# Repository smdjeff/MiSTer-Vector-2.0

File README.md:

## MisterArcade
## DE10-Nano adapter board for vector graphics output

* Modern, 3W mono onboard amplifier
* No slow or overclocked serial DACs. Latched, high speed, low cost R–2R ladder to perform digital-to-analog conversion
* Uses DE10-Nano GPIO1 2x20 connector for input from FPGA (GPIO2 remains free for standard MisterArcade RAM expansion)
* No USB latency
* JAMMA IO with ESD protection

* 10bit +/- 10v X output
* 10bit +/- 10v Y output
* 6bit 0-3.3v RED output
* 6bit 0-3.3v GREEN output
* 6bit 0-3.3v BLUE output

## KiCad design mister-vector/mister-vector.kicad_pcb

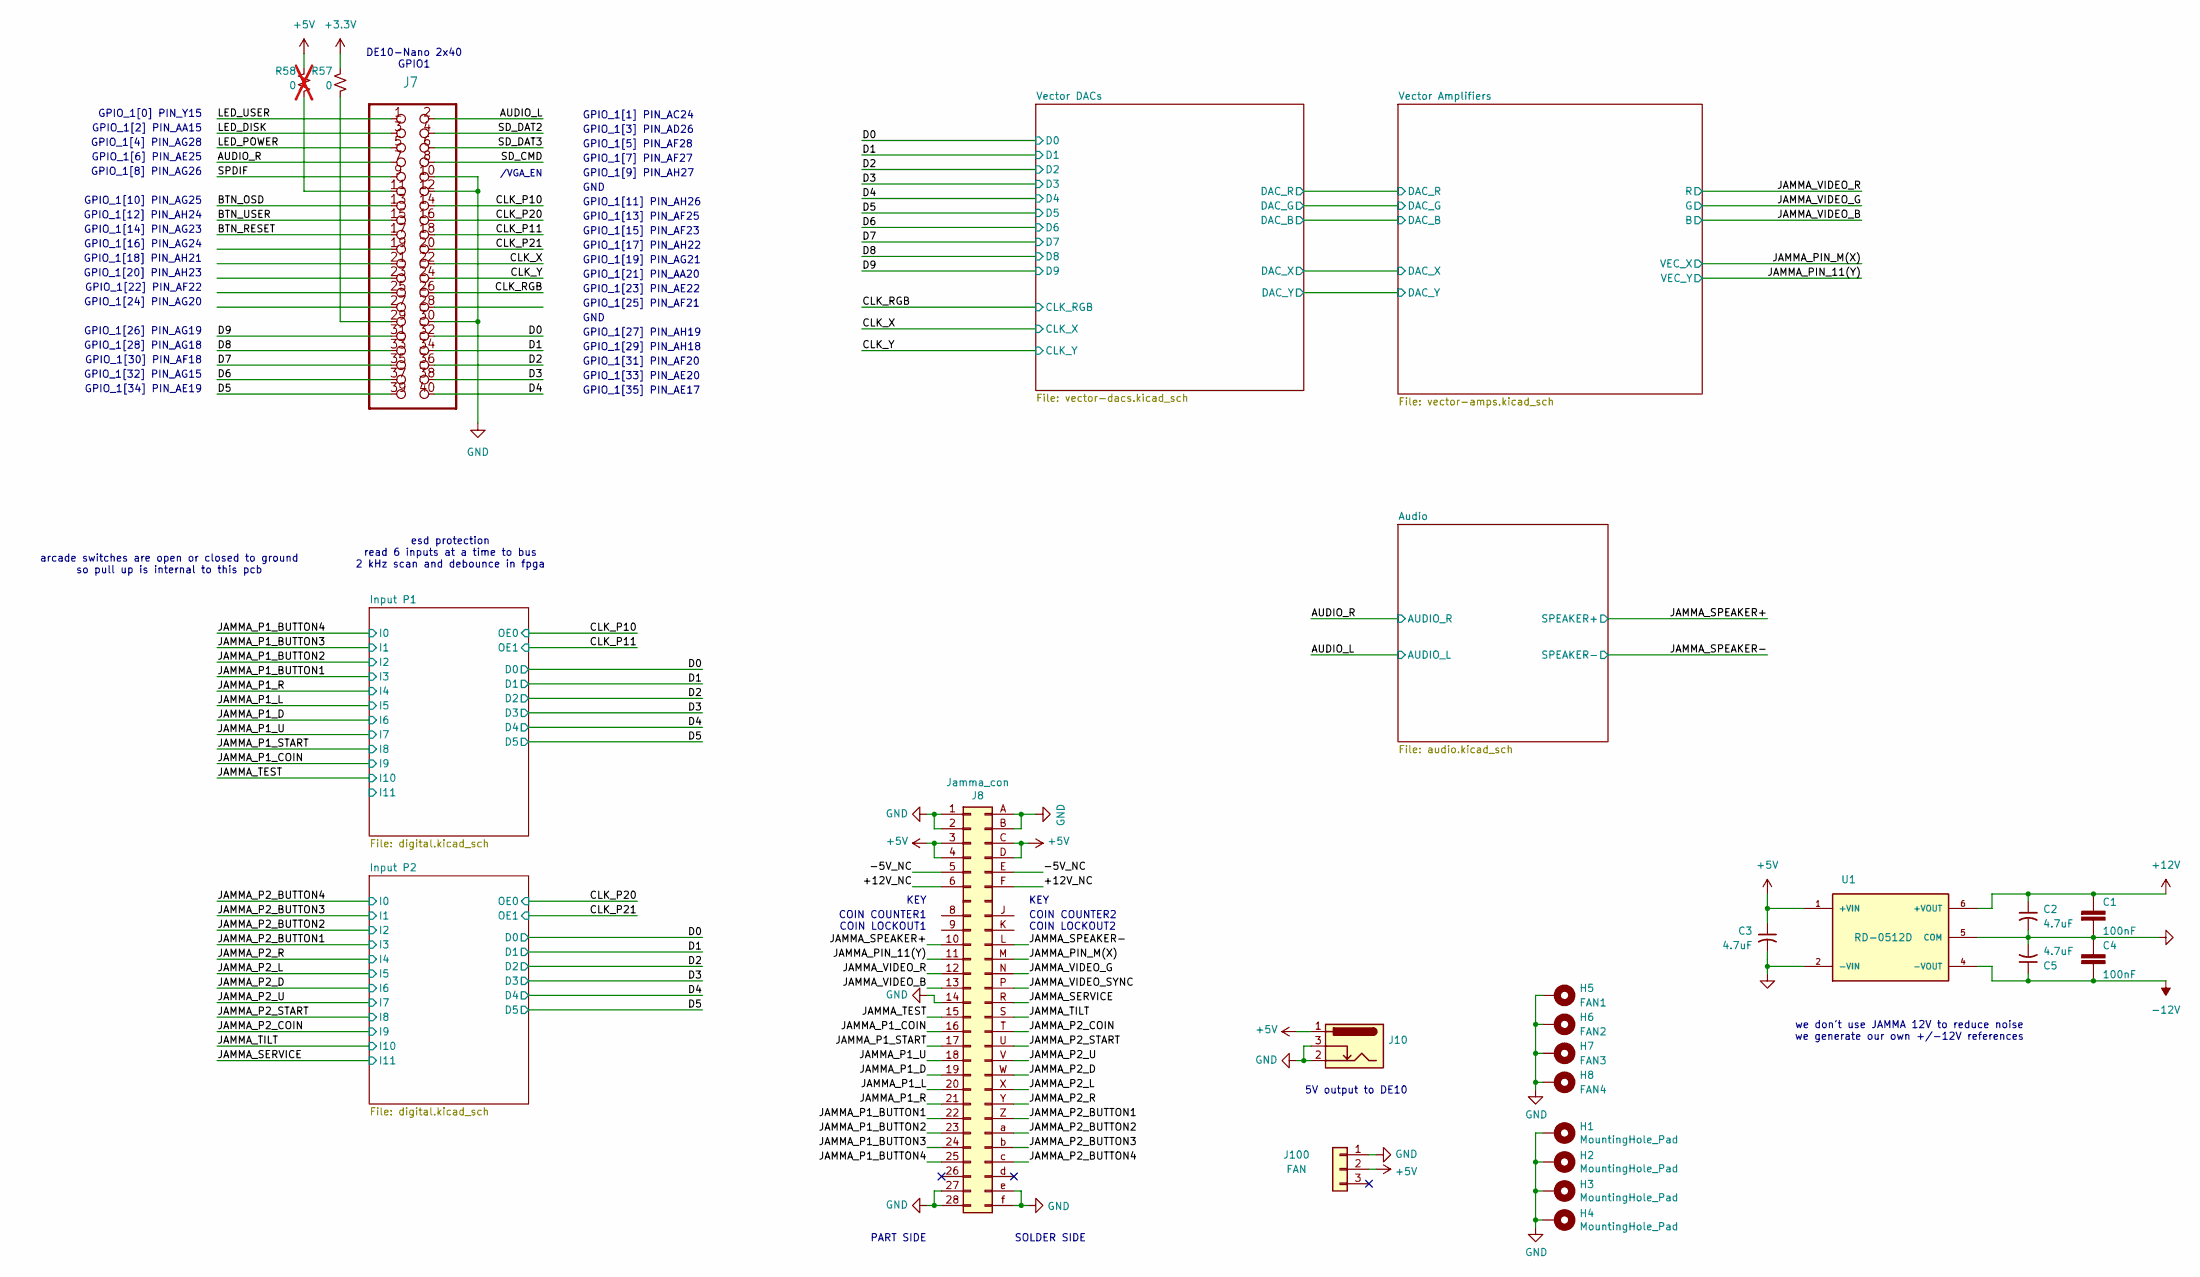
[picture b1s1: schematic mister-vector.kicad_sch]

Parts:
C1, C4: 100nF; C_0402_1005Metric; LCSC C307331
C2, C3, C5: 4.7uF; C_0805_2012Metric; LCSC C1779
H1, H2, H3, H4: MountingHole_Pad; MountingHole_3mm_Pad_Via
H5: FAN1; MountingHole_3mm
H6: FAN2; MountingHole_3mm
H7: FAN3; MountingHole_3mm
H8: FAN4; MountingHole_3mm
J7: PINHD-2X20; 2X20
J8: Jamma_con; JAMMA-56
J10: DC-005-2.5A-2.0 C319099; BarrelJack_Horizontal
J100: FAN; PinHeader_1x03_P2.54mm_Vertical
R57: 0; R_0402_1005Metric; LCSC C17168
R58: 0; R_0402_1005Metric; LCSC C17168; not fitted
U1: RD-0512D; CONV_RD-0512D; PARTREV 1; LCSC C5721603

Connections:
+3.3V: R57.1; also elsewhere on the board
+5V: C3.1, J8.3 (+5V), J8.4 (+5V), J8.C (+5V), J8.D (+5V), J10.1, J100.2, R58.1, U1.1 (+VIN); also elsewhere on the board
+12V: C1.1, C2.1, U1.6 (+VOUT); also elsewhere on the board
-12V: C4.2, C5.1, U1.4 (-VOUT); also elsewhere on the board
/+12V_NC: J8.6 (+12V), J8.F (+12V)
/-5V_NC: J8.5 (-5V), J8.E (-5V)
/AUDIO_L: J7.2; also elsewhere on the board
/AUDIO_R: J7.7; also elsewhere on the board
/BTN_OSD: J7.13
/BTN_RESET: J7.17
/BTN_USER: J7.15
/CLK_P10: J7.14; also elsewhere on the board
/CLK_P11: J7.18; also elsewhere on the board
/CLK_P20: J7.16; also elsewhere on the board
/CLK_P21: J7.20; also elsewhere on the board
/CLK_RGB: J7.26; also elsewhere on the board
/CLK_X: J7.22; also elsewhere on the board
/CLK_Y: J7.24; also elsewhere on the board
/D0: J7.32; also elsewhere on the board
/D1: J7.34; also elsewhere on the board
/D2: J7.36; also elsewhere on the board
/D3: J7.38; also elsewhere on the board
/D4: J7.40; also elsewhere on the board
/D5: J7.39; also elsewhere on the board
/D6: J7.37; also elsewhere on the board
/D7: J7.35; also elsewhere on the board
/D8: J7.33; also elsewhere on the board
/D9: J7.31; also elsewhere on the board
/JAMMA_P1_BUTTON1: J8.22 (P1_BUTTON_1); also elsewhere on the board
/JAMMA_P1_BUTTON2: J8.23 (P1_BUTTON_2); also elsewhere on the board
/JAMMA_P1_BUTTON3: J8.24 (P1_BUTTON_3); also elsewhere on the board
/JAMMA_P1_BUTTON4: J8.25 (P1_BUTTON_4); also elsewhere on the board
/JAMMA_P1_COIN: J8.16 (COIN_1); also elsewhere on the board
/JAMMA_P1_D: J8.19 (P1_DOWN); also elsewhere on the board
/JAMMA_P1_L: J8.20 (P1_LEFT); also elsewhere on the board
/JAMMA_P1_R: J8.21 (P1_RIGHT); also elsewhere on the board
/JAMMA_P1_START: J8.17 (START_1); also elsewhere on the board
/JAMMA_P1_U: J8.18 (P1_UP); also elsewhere on the board
/JAMMA_P2_BUTTON1: J8.Z (P2_BUTTON_1); also elsewhere on the board
/JAMMA_P2_BUTTON2: J8.a (P2_BUTTON_2); also elsewhere on the board
/JAMMA_P2_BUTTON3: J8.b (P2_BUTTON_3); also elsewhere on the board
/JAMMA_P2_BUTTON4: J8.c (P2_BUTTON_4); also elsewhere on the board
/JAMMA_P2_COIN: J8.T (COIN_2); also elsewhere on the board
/JAMMA_P2_D: J8.W (P2_DOWN); also elsewhere on the board
/JAMMA_P2_L: J8.X (P2_LEFT); also elsewhere on the board
/JAMMA_P2_R: J8.Y (P2_RIGHT); also elsewhere on the board
/JAMMA_P2_START: J8.U (START_2); also elsewhere on the board
/JAMMA_P2_U: J8.V (P2_UP); also elsewhere on the board
/JAMMA_PIN_11(Y): J8.11 (AUDIO+); also elsewhere on the board
/JAMMA_PIN_M(X): J8.M (TEST); also elsewhere on the board
/JAMMA_SERVICE: J8.R (SERVICE); also elsewhere on the board
/JAMMA_SPEAKER+: J8.10 (SPEAKER+); also elsewhere on the board
/JAMMA_SPEAKER-: J8.L (SPEAKER-); also elsewhere on the board
/JAMMA_TEST: J8.15 (COIN_3); also elsewhere on the board
/JAMMA_TILT: J8.S (COIN_4); also elsewhere on the board
/JAMMA_VIDEO_B: J8.13 (VIDEO_BLUE); also elsewhere on the board
/JAMMA_VIDEO_G: J8.N (VIDEO_GREEN); also elsewhere on the board
/JAMMA_VIDEO_R: J8.12 (VIDEO_RED); also elsewhere on the board
/JAMMA_VIDEO_SYNC: J8.P (VIDEO_SYNC)
/LED_DISK: J7.3
/LED_POWER: J7.5
/LED_USER: J7.1
/SD_CMD: J7.8
/SD_DAT2: J7.4
/SD_DAT3: J7.6
/SPDIF: J7.9
GND: C1.2, C2.2, C3.2, C4.1, C5.2, H1.1, H2.1, H3.1, H4.1, H5.1, H6.1, H7.1, H8.1, J7.10, J7.12, J7.30, J8.1 (GND), J8.2 (GND), J8.14 (VIDEO_GND), J8.27 (GND), J8.28 (GND), J8.A (GND), J8.B (GND), J8.e (GND), J8.f (GND), J10.2, J10.3, J100.1, U1.2 (-VIN), U1.5 (COM); also elsewhere on the board
unnamed: J7.11, R58.2
unnamed: J7.29, R57.2

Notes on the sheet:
GPIO_1[12] PIN_AH24
GPIO_1[15] PIN_AF23
GPIO_1[32] PIN_AG15
GPIO_1[7] PIN_AF27
SOLDER SIDE
GPIO_1[31] PIN_AF20
KEY
GPIO_1[27] PIN_AH19
GPIO_1[2] PIN_AA15
COIN LOCKOUT1
GPIO_1[23] PIN_AE22
GPIO_1[8] PIN_AG26
GPIO_1[29] PIN_AH18
GPIO_1[5] PIN_AF28
GPIO_1[1] PIN_AC24
GPIO_1[24] PIN_AG20
/VGA_EN
COIN LOCKOUT2
GPIO_1[25] PIN_AF21
GPIO_1[26] PIN_AG19
GND
GPIO_1[11] PIN_AH26
GPIO_1[21] PIN_AA20
GPIO_1[16] PIN_AG24
GPIO_1[0] PIN_Y15
GPIO_1[14] PIN_AG23
esd protection read 6 inputs at a time to bus 2 kHz scan and debounce in fpga
COIN COUNTER1
GPIO_1[19] PIN_AG21
GPIO_1[6] PIN_AE25
DE10-Nano 2x40 GPIO1
GPIO_1[10] PIN_AG25
GPIO_1[34] PIN_AE19
GPIO_1[35] PIN_AE17
GPIO_1[4] PIN_AG28
GPIO_1[33] PIN_AE20
GPIO_1[3] PIN_AD26
arcade switches are open or closed to ground so pull up is internal to this pcb
GPIO_1[13] PIN_AF25
GPIO_1[20] PIN_AH23

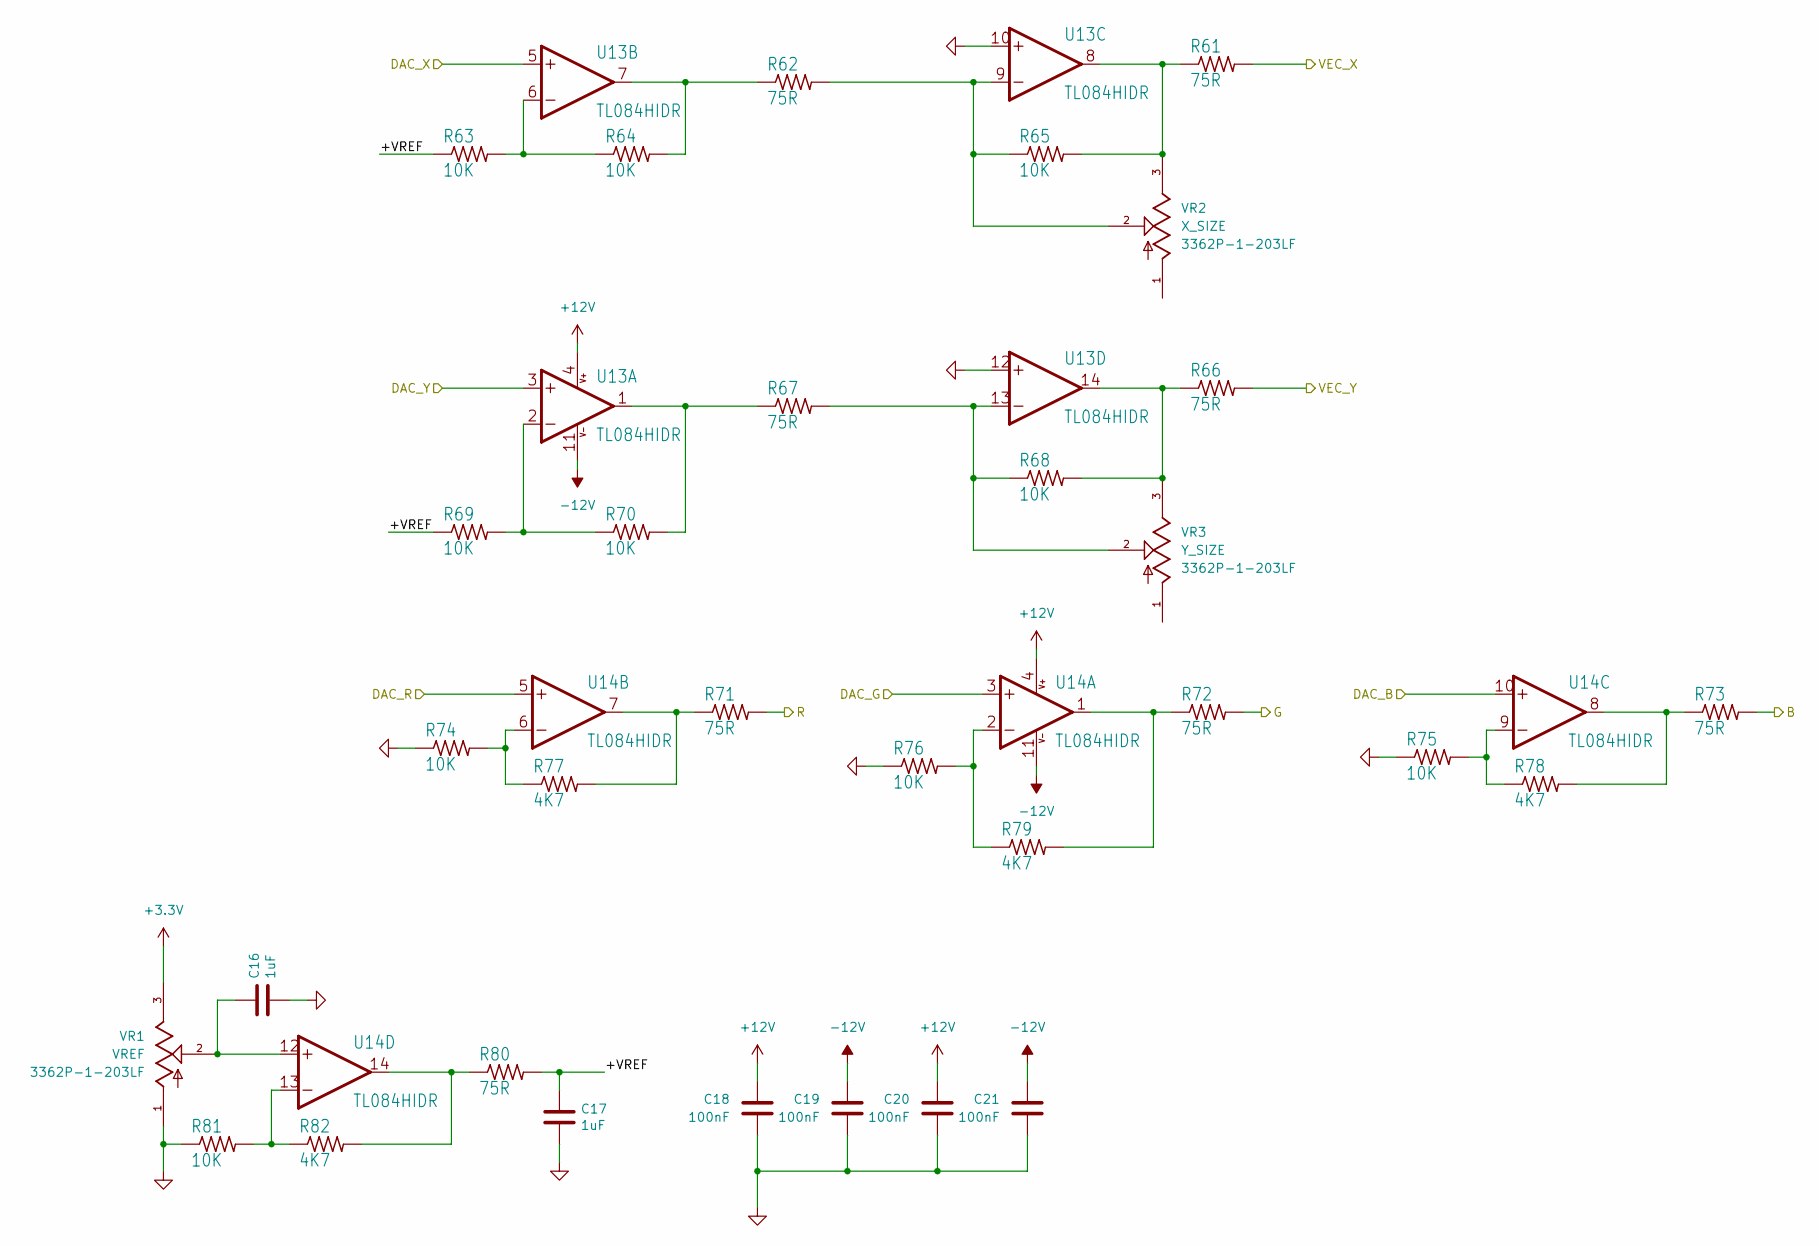
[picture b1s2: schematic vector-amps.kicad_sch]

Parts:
C16, C17: 1uF; C_0603_1608Metric; LCSC C15849
C18, C19, C20, C21: 100nF; C_0402_1005Metric; LCSC C307331
R61, R62, R66, R67, R71, R72, R73, R80: 75R; R0603; LCSC C114757
R63, R64, R65, R68, R69, R70, R74, R75, R76, R81: 10K; R0603; LCSC C25744
R77, R78, R79, R82: 4K7; R0603; LCSC C25900
U13, U14: TL084HIDR; SOIC-14_3.9x8.7mm_P1.27mm; LCSC C2878714
VR1: VREF; TRIM_3362P-1-203LF; LCSC C81263
VR2: X_SIZE; TRIM_3362P-1-203LF; LCSC C81263
VR3: Y_SIZE; TRIM_3362P-1-203LF; LCSC C81263

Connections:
+3.3V: VR1.3; also elsewhere on the board
+12V: C18.2, C20.2, U13.4 (V+), U14.4 (V+); also elsewhere on the board
-12V: C19.2, C21.2, U13.11 (V-), U14.11 (V-); also elsewhere on the board
/JAMMA_PIN_11(Y): R66.2; also elsewhere on the board
/JAMMA_PIN_M(X): R61.2; also elsewhere on the board
/JAMMA_VIDEO_B: R73.2; also elsewhere on the board
/JAMMA_VIDEO_G: R72.2; also elsewhere on the board
/JAMMA_VIDEO_R: R71.2; also elsewhere on the board
/Vector Amplifiers/+VREF: C17.1, R63.1, R69.1, R80.2
/Vector Amplifiers/DAC_B: U14.10 (+IN); also elsewhere on the board
/Vector Amplifiers/DAC_G: U14.3 (+IN); also elsewhere on the board
/Vector Amplifiers/DAC_R: U14.5 (+IN); also elsewhere on the board
/Vector Amplifiers/DAC_X: U13.5 (+IN); also elsewhere on the board
/Vector Amplifiers/DAC_Y: U13.3 (+IN); also elsewhere on the board
GND: C16.2, C17.2, C18.1, C19.1, C20.1, C21.1, R74.1, R75.1, R76.1, R81.1, U13.10 (+IN), U13.12 (+IN), VR1.1; also elsewhere on the board
unnamed: R69.2, R70.1, U13.2 (-IN)
unnamed: R67.1, R70.2, U13.1 (OUT)
unnamed: R63.2, R64.1, U13.6 (-IN)
unnamed: R62.1, R64.2, U13.7 (OUT)
unnamed: R62.2, R65.1, U13.9 (-IN), VR2.2
unnamed: R61.1, R65.2, U13.8 (OUT), VR2.3
unnamed: R67.2, R68.1, U13.13 (-IN), VR3.2
unnamed: R66.1, R68.2, U13.14 (OUT), VR3.3
unnamed: R76.2, R79.1, U14.2 (-IN)
unnamed: R72.1, R79.2, U14.1 (OUT)
unnamed: R74.2, R77.1, U14.6 (-IN)
unnamed: R71.1, R77.2, U14.7 (OUT)
unnamed: R75.2, R78.1, U14.9 (-IN)
unnamed: R73.1, R78.2, U14.8 (OUT)
unnamed: C16.1, U14.12 (+IN), VR1.2
unnamed: R81.2, R82.1, U14.13 (-IN)
unnamed: R80.1, R82.2, U14.14 (OUT)

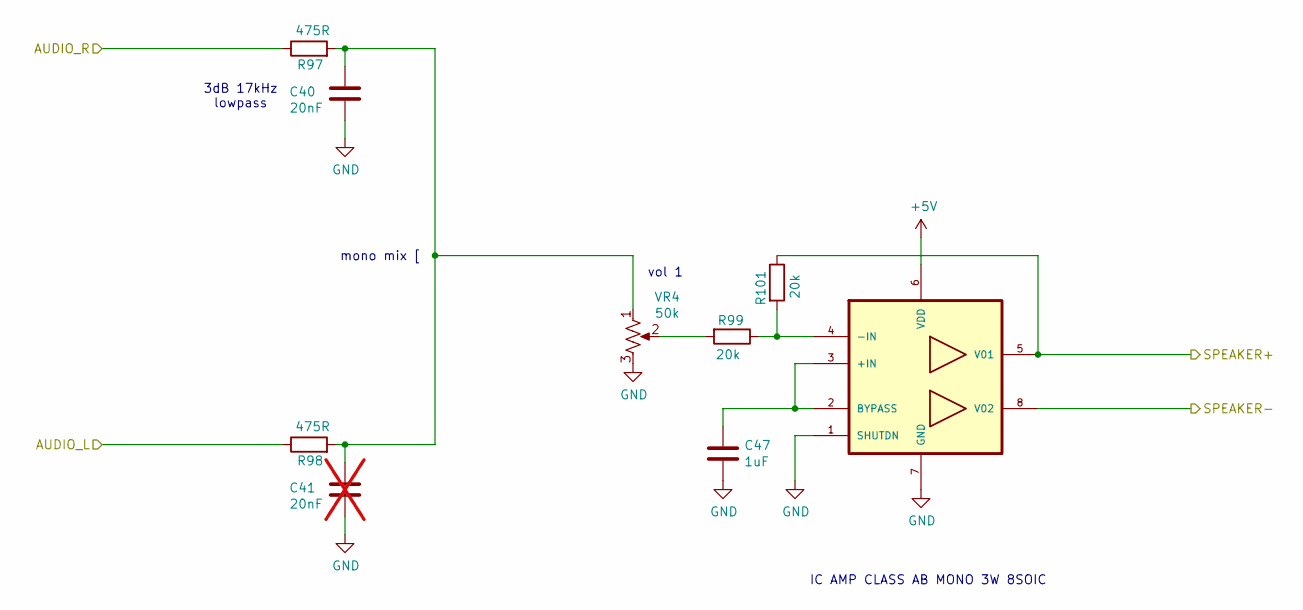
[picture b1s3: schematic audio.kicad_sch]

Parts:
C40: 20nF; C_0402_1005Metric; LCSC C5448807
C41: 20nF; C_0402_1005Metric; LCSC C5448807; not fitted
C47: 1uF; C_0603_1608Metric; LCSC C15849
R97, R98: 475R; R_0402_1005Metric; LCSC C137975
R99, R101: 20k; R_0402_1005Metric; LCSC C25765
U12: LM4871MX_NOPB; SOIC127P599X175-8N; LCSC C7554
VR4: 50k; PTV09A4020FB103; Manufacturer_Part_Number PTV09A-4020U-A503; Mouser Part Number 652-PTV09A-4020UA503

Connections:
+5V: U12.6 (VDD); also elsewhere on the board
/AUDIO_L: R98.1; also elsewhere on the board
/AUDIO_R: R97.1; also elsewhere on the board
/JAMMA_SPEAKER+: R101.1, U12.5 (V01); also elsewhere on the board
/JAMMA_SPEAKER-: U12.8 (V02); also elsewhere on the board
GND: C40.1, C41.1, C47.2, U12.1 (SHUTDN), U12.7 (GND), VR4.3; also elsewhere on the board
unnamed: C40.2, C41.2, R97.2, R98.2, VR4.1
unnamed: R99.2, VR4.2
unnamed: C47.1, U12.2 (BYPASS), U12.3 (+IN)
unnamed: R99.1, R101.2, U12.4 (-IN)

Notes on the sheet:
3dB 17kHz lowpass
IC AMP CLASS AB MONO 3W 8SOIC
vol 1
mono mix [

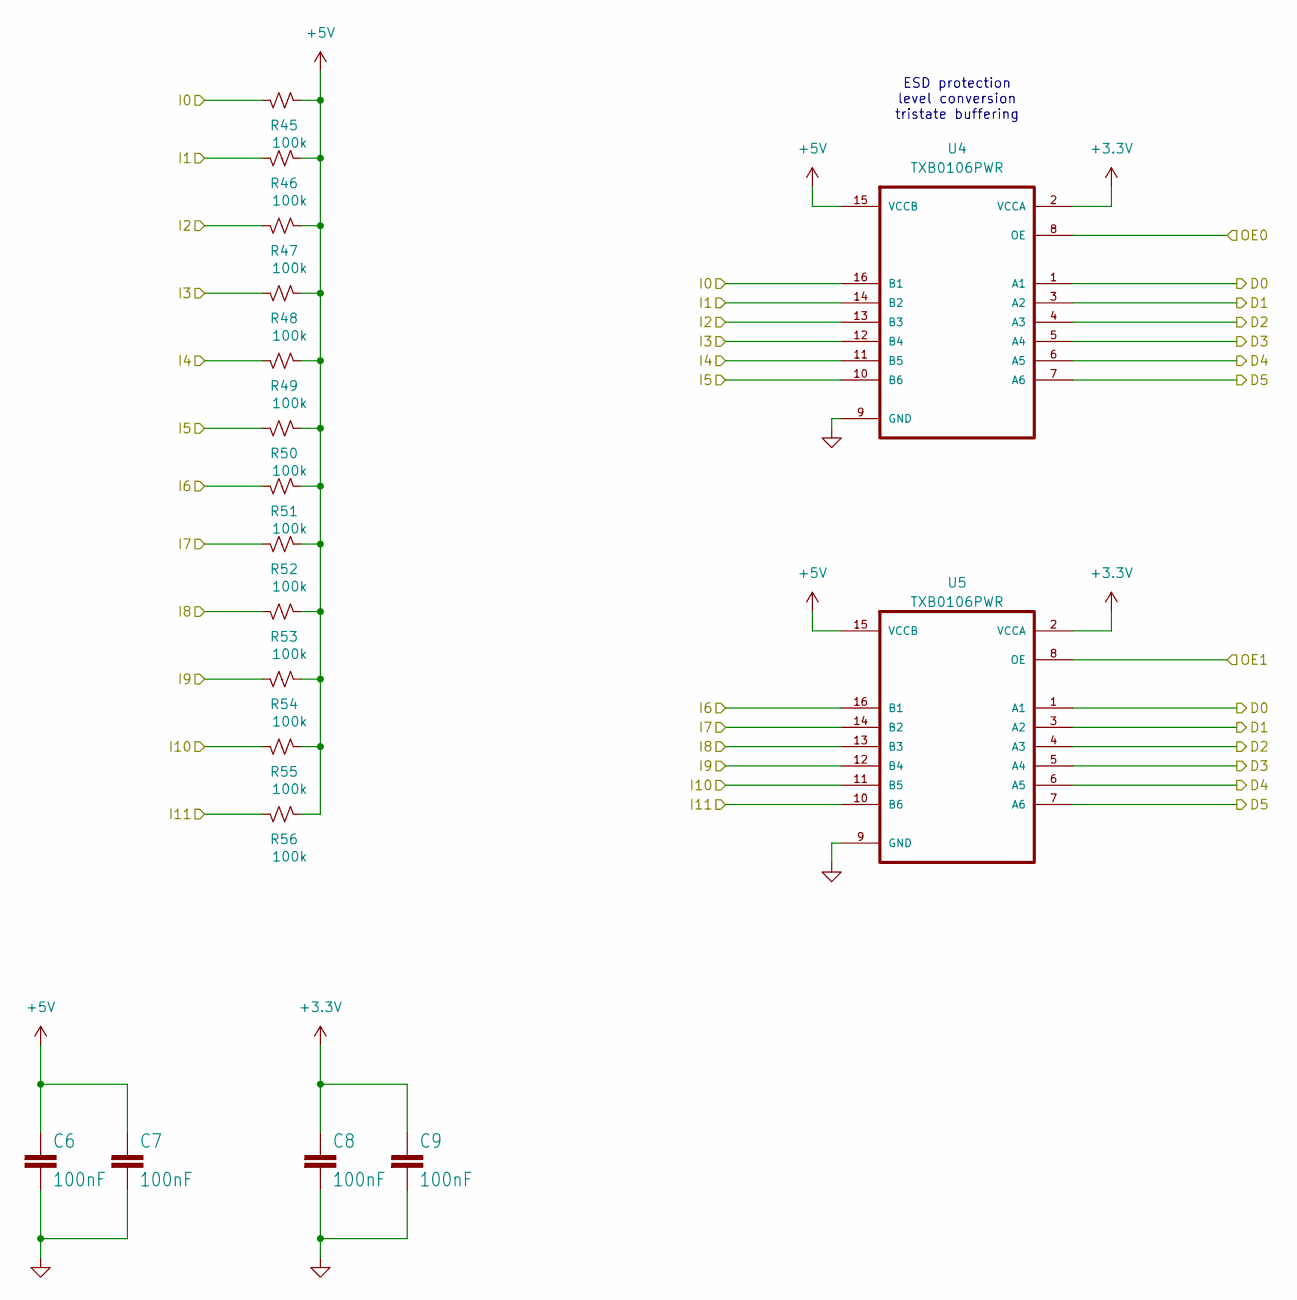
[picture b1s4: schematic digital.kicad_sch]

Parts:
C6, C7, C8, C9: 100nF; C_0402_1005Metric; LCSC C307331
R45, R46, R47, R48, R49, R50, R51, R52, R53, R54, R55, R56: 100k; R_0402_1005Metric; LCSC C25741
U4, U5: TXB0106PWR; SOP65P640X120-16N; DigiKey_Part_Number 296-23759-2-ND

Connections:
+3.3V: C8.1, C9.1, U4.2 (VCCA), U5.2 (VCCA); also elsewhere on the board
+5V: C6.1, C7.1, R45.2, R46.2, R47.2, R48.2, R49.2, R50.2, R51.2, R52.2, R53.2, R54.2, R55.2, R56.2, U4.15 (VCCB), U5.15 (VCCB); also elsewhere on the board
/CLK_P10: U4.8 (OE); also elsewhere on the board
/CLK_P11: U5.8 (OE); also elsewhere on the board
/D0: U4.1 (A1), U5.1 (A1); also elsewhere on the board
/D1: U4.3 (A2), U5.3 (A2); also elsewhere on the board
/D2: U4.4 (A3), U5.4 (A3); also elsewhere on the board
/D3: U4.5 (A4), U5.5 (A4); also elsewhere on the board
/D4: U4.6 (A5), U5.6 (A5); also elsewhere on the board
/D5: U4.7 (A6), U5.7 (A6); also elsewhere on the board
/Input P1/I11: R56.1, U5.10 (B6)
/JAMMA_P1_BUTTON1: R48.1, U4.12 (B4); also elsewhere on the board
/JAMMA_P1_BUTTON2: R47.1, U4.13 (B3); also elsewhere on the board
/JAMMA_P1_BUTTON3: R46.1, U4.14 (B2); also elsewhere on the board
/JAMMA_P1_BUTTON4: R45.1, U4.16 (B1); also elsewhere on the board
/JAMMA_P1_COIN: R54.1, U5.12 (B4); also elsewhere on the board
/JAMMA_P1_D: R51.1, U5.16 (B1); also elsewhere on the board
/JAMMA_P1_L: R50.1, U4.10 (B6); also elsewhere on the board
/JAMMA_P1_R: R49.1, U4.11 (B5); also elsewhere on the board
/JAMMA_P1_START: R53.1, U5.13 (B3); also elsewhere on the board
/JAMMA_P1_U: R52.1, U5.14 (B2); also elsewhere on the board
/JAMMA_TEST: R55.1, U5.11 (B5); also elsewhere on the board
GND: C6.2, C7.2, C8.2, C9.2, U4.9 (GND), U5.9 (GND); also elsewhere on the board

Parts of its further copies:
C10, C11, C12, C13: 100nF; C_0402_1005Metric; LCSC C307331
R59, R60, R83, R84, R85, R86, R87, R88, R89, R90, R91, R92: 100k; R_0402_1005Metric; LCSC C25741
U6, U10: TXB0106PWR; SOP65P640X120-16N; DigiKey_Part_Number 296-23759-2-ND

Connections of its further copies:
+3.3V: C12.1, C13.1, U6.2 (VCCA), U10.2 (VCCA); also elsewhere on the board
+5V: C10.1, C11.1, R59.2, R60.2, R83.2, R84.2, R85.2, R86.2, R87.2, R88.2, R89.2, R90.2, R91.2, R92.2, U6.15 (VCCB), U10.15 (VCCB); also elsewhere on the board
/CLK_P20: U6.8 (OE); also elsewhere on the board
/CLK_P21: U10.8 (OE); also elsewhere on the board
/D0: U6.1 (A1), U10.1 (A1); also elsewhere on the board
/D1: U6.3 (A2), U10.3 (A2); also elsewhere on the board
/D2: U6.4 (A3), U10.4 (A3); also elsewhere on the board
/D3: U6.5 (A4), U10.5 (A4); also elsewhere on the board
/D4: U6.6 (A5), U10.6 (A5); also elsewhere on the board
/D5: U6.7 (A6), U10.7 (A6); also elsewhere on the board
/JAMMA_P2_BUTTON1: R84.1, U6.12 (B4); also elsewhere on the board
/JAMMA_P2_BUTTON2: R83.1, U6.13 (B3); also elsewhere on the board
/JAMMA_P2_BUTTON3: R60.1, U6.14 (B2); also elsewhere on the board
/JAMMA_P2_BUTTON4: R59.1, U6.16 (B1); also elsewhere on the board
/JAMMA_P2_COIN: R90.1, U10.12 (B4); also elsewhere on the board
/JAMMA_P2_D: R87.1, U10.16 (B1); also elsewhere on the board
/JAMMA_P2_L: R86.1, U6.10 (B6); also elsewhere on the board
/JAMMA_P2_R: R85.1, U6.11 (B5); also elsewhere on the board
/JAMMA_P2_START: R89.1, U10.13 (B3); also elsewhere on the board
/JAMMA_P2_U: R88.1, U10.14 (B2); also elsewhere on the board
/JAMMA_SERVICE: R92.1, U10.10 (B6); also elsewhere on the board
/JAMMA_TILT: R91.1, U10.11 (B5); also elsewhere on the board
GND: C10.2, C11.2, C12.2, C13.2, U6.9 (GND), U10.9 (GND); also elsewhere on the board

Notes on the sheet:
ESD protection level conversion tristate buffering

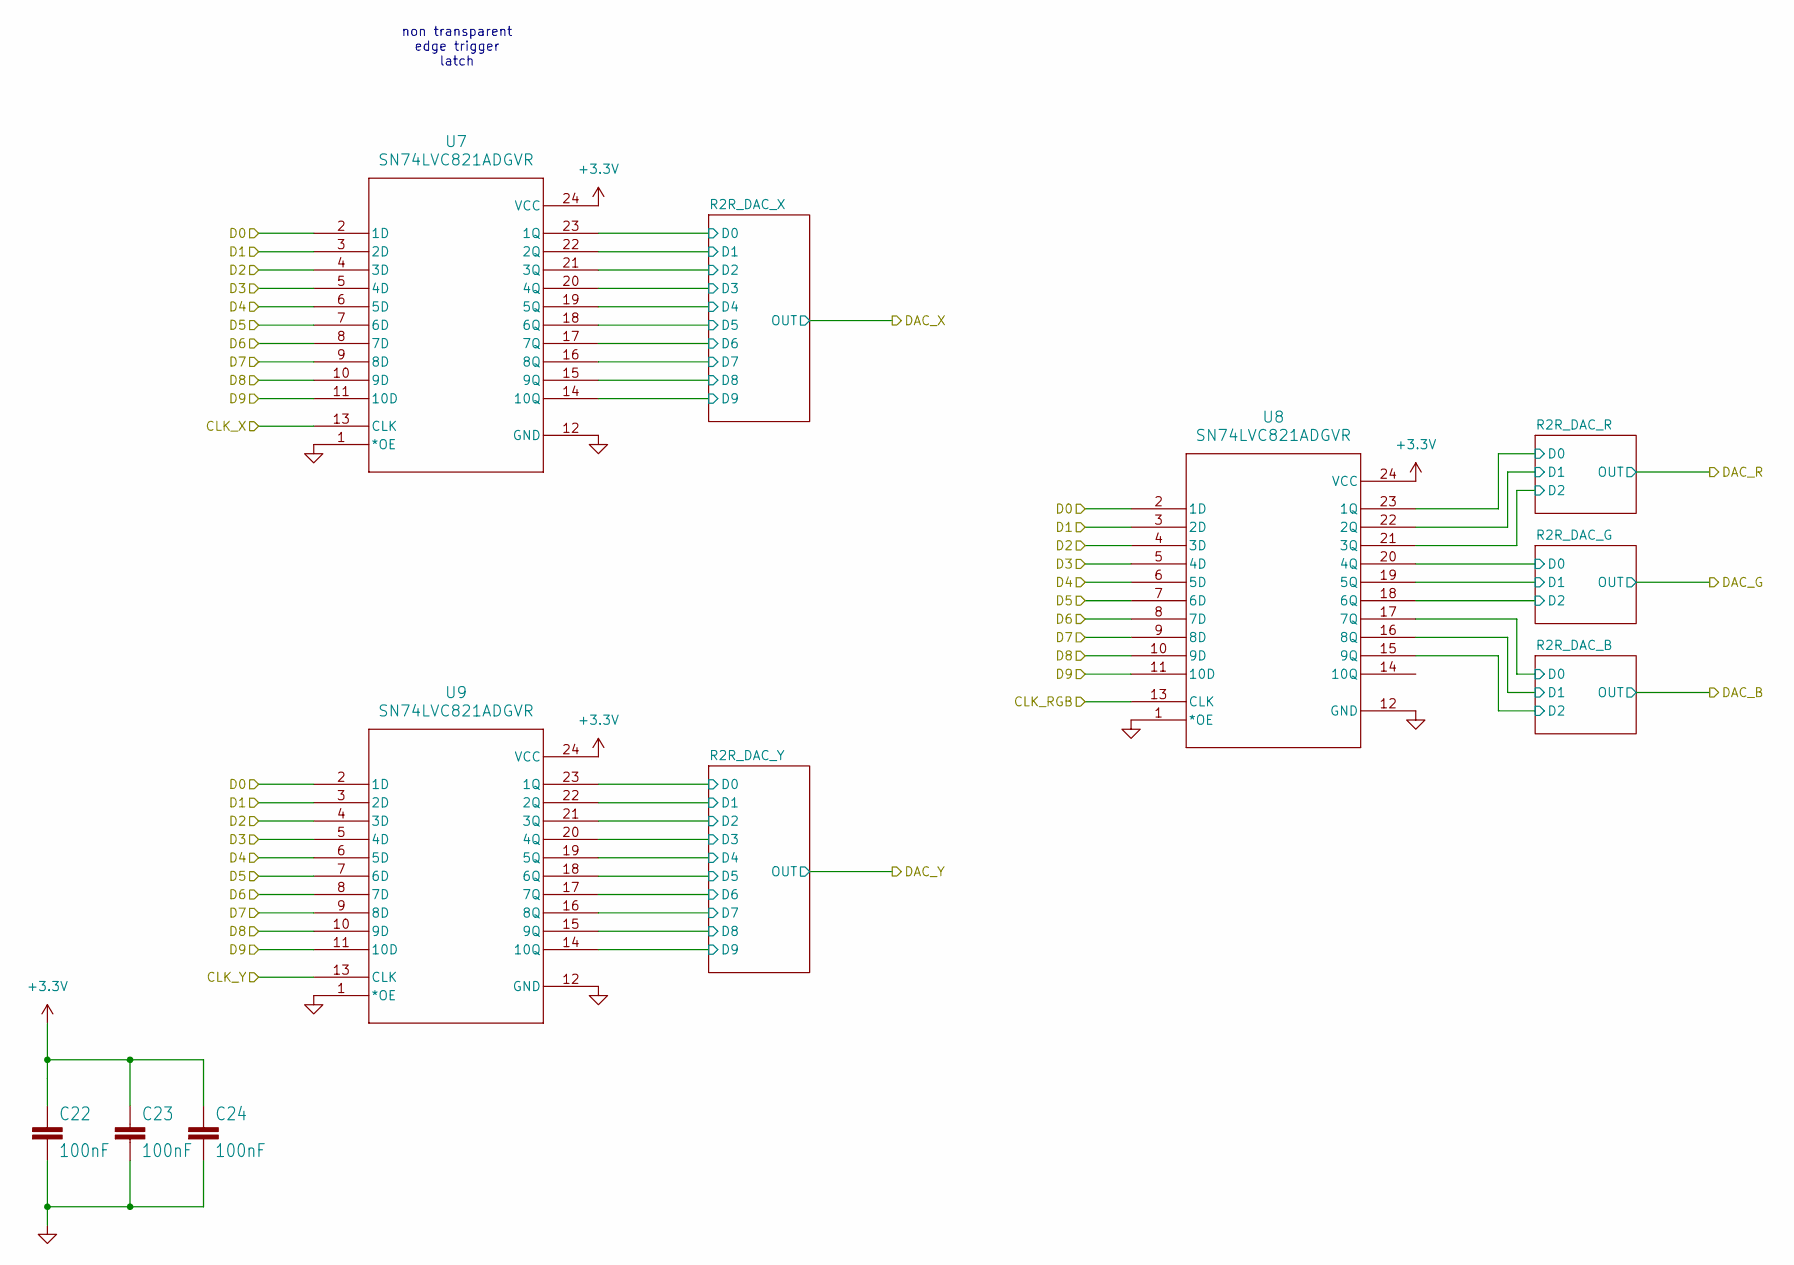
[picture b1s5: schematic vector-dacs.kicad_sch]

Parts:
C22, C23, C24: 100nF; C_0402_1005Metric; LCSC C307331
U7, U8, U9: SN74LVC821ADGVR; LCSC C2869439

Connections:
+3.3V: C22.1, C23.1, C24.1, U7.24 (VCC), U8.24 (VCC), U9.24 (VCC); also elsewhere on the board
/CLK_RGB: U8.13 (CLK); also elsewhere on the board
/CLK_X: U7.13 (CLK); also elsewhere on the board
/CLK_Y: U9.13 (CLK); also elsewhere on the board
/D0: U7.2 (1D), U8.2 (1D), U9.2 (1D); also elsewhere on the board
/D1: U7.3 (2D), U8.3 (2D), U9.3 (2D); also elsewhere on the board
/D2: U7.4 (3D), U8.4 (3D), U9.4 (3D); also elsewhere on the board
/D3: U7.5 (4D), U8.5 (4D), U9.5 (4D); also elsewhere on the board
/D4: U7.6 (5D), U8.6 (5D), U9.6 (5D); also elsewhere on the board
/D5: U7.7 (6D), U8.7 (6D), U9.7 (6D); also elsewhere on the board
/D6: U7.8 (7D), U8.8 (7D), U9.8 (7D); also elsewhere on the board
/D7: U7.9 (8D), U8.9 (8D), U9.9 (8D); also elsewhere on the board
/D8: U7.10 (9D), U8.10 (9D), U9.10 (9D); also elsewhere on the board
/D9: U7.11 (10D), U8.11 (10D), U9.11 (10D); also elsewhere on the board
/Vector DACs/R2R_DAC_B/D0: U8.17 (7Q); also elsewhere on the board
/Vector DACs/R2R_DAC_B/D1: U8.16 (8Q); also elsewhere on the board
/Vector DACs/R2R_DAC_B/D2: U8.15 (9Q); also elsewhere on the board
/Vector DACs/R2R_DAC_G/D0: U8.20 (4Q); also elsewhere on the board
/Vector DACs/R2R_DAC_G/D1: U8.19 (5Q); also elsewhere on the board
/Vector DACs/R2R_DAC_G/D2: U8.18 (6Q); also elsewhere on the board
/Vector DACs/R2R_DAC_R/D0: U8.23 (1Q); also elsewhere on the board
/Vector DACs/R2R_DAC_R/D1: U8.22 (2Q); also elsewhere on the board
/Vector DACs/R2R_DAC_R/D2: U8.21 (3Q); also elsewhere on the board
/Vector DACs/R2R_DAC_X/D0: U7.23 (1Q); also elsewhere on the board
/Vector DACs/R2R_DAC_X/D1: U7.22 (2Q); also elsewhere on the board
/Vector DACs/R2R_DAC_X/D2: U7.21 (3Q); also elsewhere on the board
/Vector DACs/R2R_DAC_X/D3: U7.20 (4Q); also elsewhere on the board
/Vector DACs/R2R_DAC_X/D4: U7.19 (5Q); also elsewhere on the board
/Vector DACs/R2R_DAC_X/D5: U7.18 (6Q); also elsewhere on the board
/Vector DACs/R2R_DAC_X/D6: U7.17 (7Q); also elsewhere on the board
/Vector DACs/R2R_DAC_X/D7: U7.16 (8Q); also elsewhere on the board
/Vector DACs/R2R_DAC_X/D8: U7.15 (9Q); also elsewhere on the board
/Vector DACs/R2R_DAC_X/D9: U7.14 (10Q); also elsewhere on the board
/Vector DACs/R2R_DAC_Y/D0: U9.23 (1Q); also elsewhere on the board
/Vector DACs/R2R_DAC_Y/D1: U9.22 (2Q); also elsewhere on the board
/Vector DACs/R2R_DAC_Y/D2: U9.21 (3Q); also elsewhere on the board
/Vector DACs/R2R_DAC_Y/D3: U9.20 (4Q); also elsewhere on the board
/Vector DACs/R2R_DAC_Y/D4: U9.19 (5Q); also elsewhere on the board
/Vector DACs/R2R_DAC_Y/D5: U9.18 (6Q); also elsewhere on the board
/Vector DACs/R2R_DAC_Y/D6: U9.17 (7Q); also elsewhere on the board
/Vector DACs/R2R_DAC_Y/D7: U9.16 (8Q); also elsewhere on the board
/Vector DACs/R2R_DAC_Y/D8: U9.15 (9Q); also elsewhere on the board
/Vector DACs/R2R_DAC_Y/D9: U9.14 (10Q); also elsewhere on the board
GND: C22.2, C23.2, C24.2, U7.1 (*OE), U7.12 (GND), U8.1 (*OE), U8.12 (GND), U9.1 (*OE), U9.12 (GND); also elsewhere on the board

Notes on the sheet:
non transparent edge trigger latch

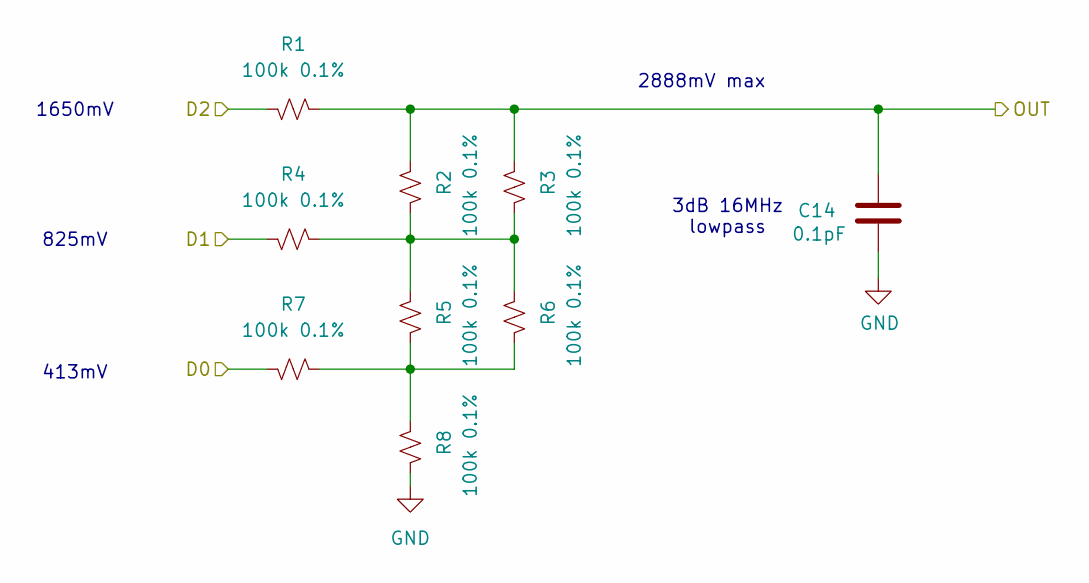
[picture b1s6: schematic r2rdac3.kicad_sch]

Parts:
C14: 0.1pF; C_0402_1005Metric; LCSC C5448807
R1, R2, R3, R4, R5, R6, R7, R8: 100k 0.1%; R_0402_1005Metric; LCSC C852472

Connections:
/Vector Amplifiers/DAC_B: C14.2, R1.1, R2.1, R3.1; also elsewhere on the board
/Vector DACs/R2R_DAC_B/D0: R7.2; also elsewhere on the board
/Vector DACs/R2R_DAC_B/D1: R4.2; also elsewhere on the board
/Vector DACs/R2R_DAC_B/D2: R1.2; also elsewhere on the board
GND: C14.1, R8.2; also elsewhere on the board
unnamed: R2.2, R3.2, R4.1, R5.1, R6.1
unnamed: R5.2, R6.2, R7.1, R8.1

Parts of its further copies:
C15, C27: 0.1pF; C_0402_1005Metric; LCSC C5448807
R9, R10, R11, R12, R13, R14, R15, R16, R17, R18, R19, R20, R21, R22, R23, R24: 100k 0.1%; R_0402_1005Metric; LCSC C852472

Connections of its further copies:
/Vector Amplifiers/DAC_G: C15.2, R9.1, R10.1, R11.1; also elsewhere on the board
/Vector Amplifiers/DAC_R: C27.2, R17.1, R18.1, R19.1; also elsewhere on the board
/Vector DACs/R2R_DAC_G/D0: R15.2; also elsewhere on the board
/Vector DACs/R2R_DAC_G/D1: R12.2; also elsewhere on the board
/Vector DACs/R2R_DAC_G/D2: R9.2; also elsewhere on the board
/Vector DACs/R2R_DAC_R/D0: R23.2; also elsewhere on the board
/Vector DACs/R2R_DAC_R/D1: R20.2; also elsewhere on the board
/Vector DACs/R2R_DAC_R/D2: R17.2; also elsewhere on the board
GND: C15.1, C27.1, R16.2, R24.2; also elsewhere on the board
unnamed: R10.2, R11.2, R12.1, R13.1, R14.1
unnamed: R13.2, R14.2, R15.1, R16.1
unnamed: R18.2, R19.2, R20.1, R21.1, R22.1
unnamed: R21.2, R22.2, R23.1, R24.1

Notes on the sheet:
2888mV max
3dB 16MHz lowpass
413mV
825mV
1650mV

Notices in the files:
mister-vector/mister-vector.kicad_pcb:
JAMMA V1.0 ©2025
